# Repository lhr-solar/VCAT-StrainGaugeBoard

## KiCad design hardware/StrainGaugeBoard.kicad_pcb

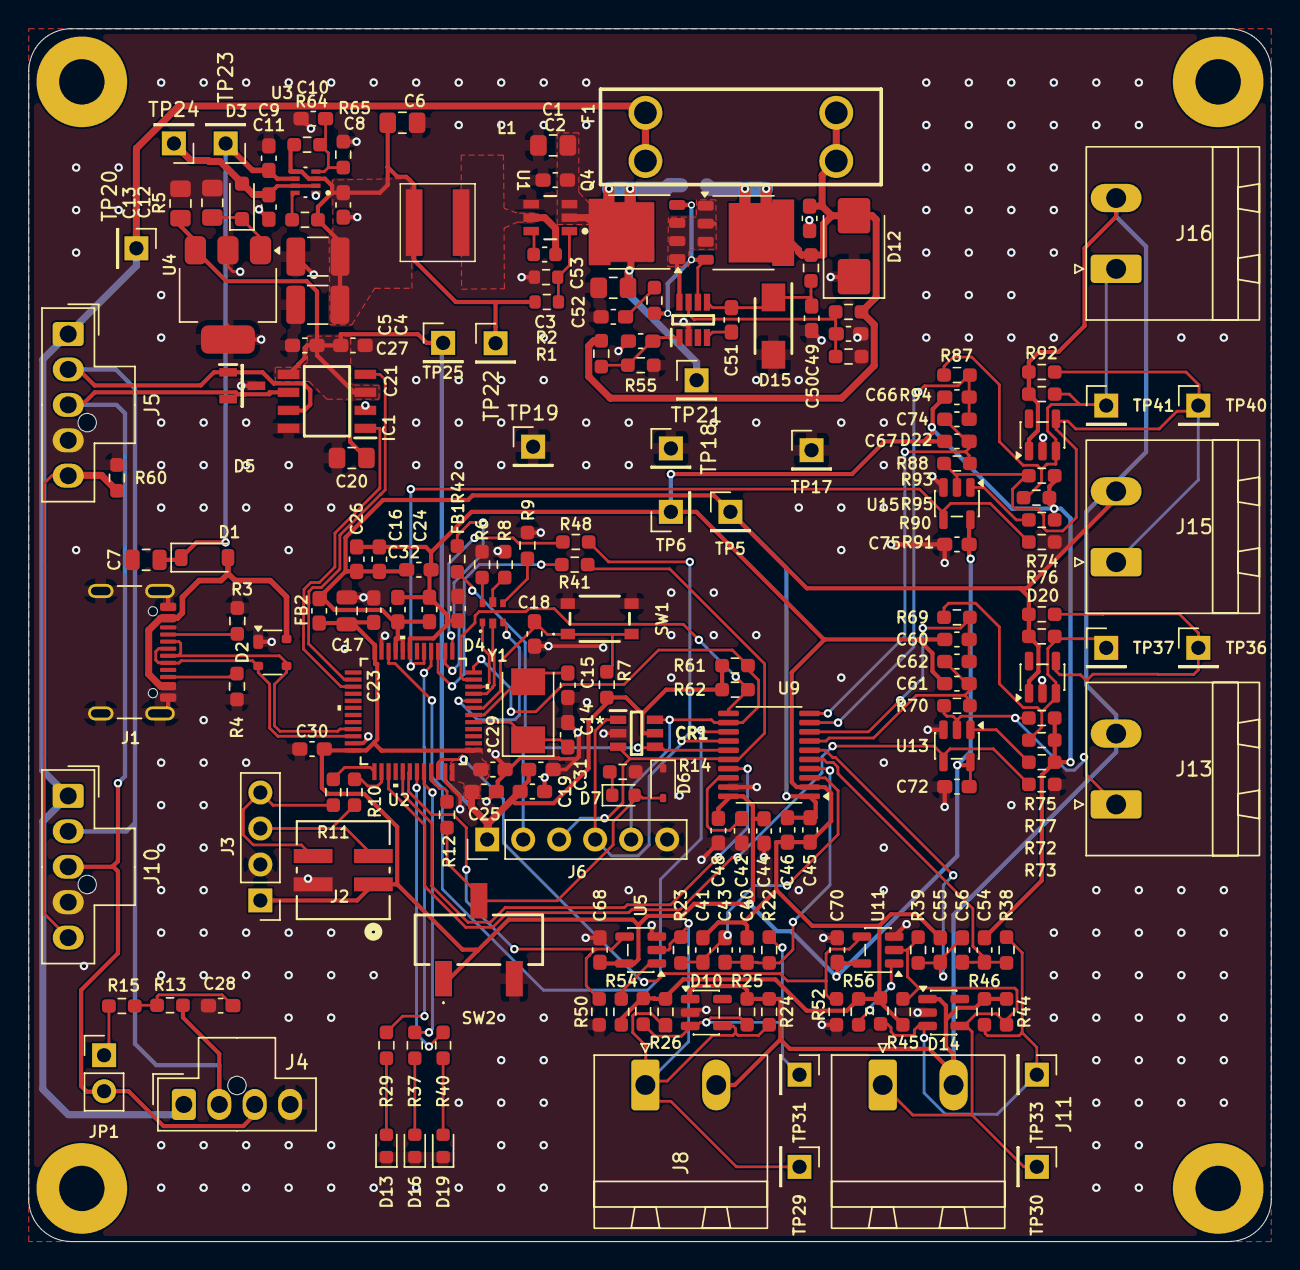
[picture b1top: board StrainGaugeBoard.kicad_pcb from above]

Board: 2 copper layers, 87.7 x 85.6 mm, 198 parts (1 on the bottom side), 92 nets.

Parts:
C1: 4.7u; C_0805_2012Metric_Pad1.18x1.45mm_HandSolder
C2: 100n; C_0603_1608Metric_Pad1.08x0.95mm_HandSolder
C3: 100n; C_0603_1608Metric
C4, C5: 22u; C_1210_3225Metric_Pad1.33x2.70mm_HandSolder
C6: 3.3u; C_0805_2012Metric_Pad1.18x1.45mm_HandSolder
C7: 10u; C_0805_2012Metric
C8, C9, C10, C11, C21, C27, C28, C45, C48, C49, C57, C58, C68, C70, C72, C75: 0.1u; C_0603_1608Metric_Pad1.08x0.95mm_HandSolder
C12, C13, C20, C53: 10u; C_0805_2012Metric_Pad1.18x1.45mm_HandSolder
C14, C15: 26p; C_0603_1608Metric_Pad1.08x0.95mm_HandSolder
C16, C18, C19, C22, C23, C25, C29, C30, C31: 0.1uF; C_0603_1608Metric_Pad1.08x0.95mm_HandSolder
C17: 10uF; C_0805_2012Metric
C24, C26: 1uF; C_0603_1608Metric_Pad1.08x0.95mm_HandSolder
C32: 100nF; C_0603_1608Metric_Pad1.08x0.95mm_HandSolder
C40, C41, C54, C55, C60, C61, C66, C67: 1n; C_0603_1608Metric_Pad1.08x0.95mm_HandSolder
C42, C51: 220n; C_0603_1608Metric_Pad1.08x0.95mm_HandSolder
C43, C52, C56, C62, C74: 10n; C_0603_1608Metric_Pad1.08x0.95mm_HandSolder
C44, C46, C50: 1u; C_0603_1608Metric_Pad1.08x0.95mm_HandSolder
CR1: D5V0P4UR6SO-7
D1: D_Schottky; D_SOD-123
D2: SP0503BAHT; SOT-143
D3: SBA130CH-AU_R1_000A1; D_SOD-323_HandSoldering
D4: RGB_LED
D5: CDSOT23-T24CAN
D6: TVS; D_SOD-323
D7, D13, D16, D19: LED; LED_0603_1608Metric
D10, D14, D20, D22: ESDA5V3SC5; SOT-23-5
D12: SMBJ15CA; D_SMB
D15: SMAF4758A; SODFL5026X125N
F1: 1A; Fuse-3557-2
FB1, FB2: FerriteBead; C_0603_1608Metric_Pad1.08x0.95mm_HandSolder
H1, H2, H3, H4: MountingHole_3.2mm_M3_Pad
IC1: TCAN3413DR
IC3: LM74502DDFR
J1: USB_C_Receptacle_USB2.0_16P; USB_C_Receptacle_GCT_USB4105-xx-A_16P_TopMnt_Horizontal
J2: SWD_Header; SWD_Conn
J3: SWD; PinHeader_1x04_P2.54mm_Vertical
J4: CAN_DEBUG; Molex_Nano-Fit_105309-xx04_1x04_P2.50mm_Vertical
J5: CAN_IN; Molex_Nano-Fit_105309-xx05_1x05_P2.50mm_Vertical
J6: Conn_01x06; PinHeader_1x06_P2.54mm_Vertical
J8, J11, J13: Gauge; PhoenixContact_MSTBA_2,5_2-G_1x02_P5.00mm_Horizontal
J10: CAN_OUT; Molex_Nano-Fit_105309-xx05_1x05_P2.50mm_Vertical
J15: Gauge A; PhoenixContact_MSTBA_2,5_2-G_1x02_P5.00mm_Horizontal
J16: Gauge B; PhoenixContact_MSTBA_2,5_2-G_1x02_P5.00mm_Horizontal
JP1: TRM; PinHeader_1x02_P2.54mm_Vertical
JP2: SolderJumper_2_Open; SolderJumper-2_P1.3mm_Open_RoundedPad1.0x1.5mm
L1: 8.2u; XAL5050822MEC
Q3, Q4: PSMN012-100YS; LFPAK56
R1: 100k; R_0603_1608Metric
R2: 19.1k; R_0603_1608Metric
R3, R4: 5.1k; R_0603_1608Metric_Pad0.98x0.95mm_HandSolder
R5, R7, R12, R35, R61, R62: 10k; R_0603_1608Metric_Pad0.98x0.95mm_HandSolder
R6, R8, R9, R14, R22, R23, R29, R37, R38, R39, R40, R69, R70, R87, R88: 1k; R_0603_1608Metric_Pad0.98x0.95mm_HandSolder
R10, R11, R41, R42, R48: 22; R_0603_1608Metric_Pad0.98x0.95mm_HandSolder
R13, R15: 60; R_0603_1608Metric_Pad0.98x0.95mm_HandSolder
R24, R25, R26, R27, R44, R45, R46, R47, R74, R75, R76, R77, R92, R93, R94, R95: 350; R_0603_1608Metric_Pad0.98x0.95mm_HandSolder
R36: 33; R_0603_1608Metric_Pad0.98x0.95mm_HandSolder
R49, R50, R52, R53, R73, R91: 100k; R_0603_1608Metric_Pad0.98x0.95mm_HandSolder
R51: 7.32k; R_0603_1608Metric_Pad0.98x0.95mm_HandSolder
R54, R56, R72, R90: 174k; R_0603_1608Metric_Pad0.98x0.95mm_HandSolder
R55: 15.8k; R_0603_1608Metric_Pad0.98x0.95mm_HandSolder
R60: 0; R_0603_1608Metric_Pad0.98x0.95mm_HandSolder
R64: 16k; R_0603_1608Metric_Pad0.98x0.95mm_HandSolder
R65: 4.7k; R_0603_1608Metric_Pad0.98x0.95mm_HandSolder
SW1: Reset; TL3365AF180QG
SW2: SW_SPDT; BootSW
TP5: VDDA; PinHeader_1x01_P2.54mm_Vertical
TP6: GNDA; PinHeader_1x01_P2.54mm_Vertical
TP17: Power TestPoint; PinHeader_1x01_P2.54mm_Vertical
TP18: MCU TestPoint; PinHeader_1x01_P2.54mm_Vertical
TP19: CAN TestPoint; PinHeader_1x01_P2.54mm_Vertical
TP20: +12V; PinHeader_1x01_P2.54mm_Vertical
TP21: +12V_PP; PinHeader_1x01_P2.54mm_Vertical
TP22: +5V_BUCK; PinHeader_1x01_P2.54mm_Vertical
TP23: +USBC_5V; PinHeader_1x01_P2.54mm_Vertical
TP24: MUX_OUT; PinHeader_1x01_P2.54mm_Vertical
TP25: LDO_OUT_TestPoint; PinHeader_1x01_P2.54mm_Vertical
TP29, TP30, TP36, TP40: SIG+; PinHeader_1x01_P2.54mm_Vertical
TP31, TP33, TP37, TP41: SIG-; PinHeader_1x01_P2.54mm_Vertical
U1: LMR51635XDDCR; DDC0006A-MFG
U2: STM32G473CETx; 48PinMCU
U3: TPS2117DRLR
U4: MCP1826S; SOT-223-3_TabPin2
U5, U11, U13, U15: TS5A3166DBVR; SOT-23-5
U9: ADS131M04xPW; TSSOP-20_4.4x6.5mm_P0.65mm
Y1: Crystal; Crystal_SMD_Abracon_ABM3-2Pin_5.0x3.2mm

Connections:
+3.3V: C13.2, C17.1, C19.1, C20.1, C21.1, C23.1, C25.1, C27.1, C29.1, C30.1, C31.1, C44.1, C48.1, C68.2, C70.2, C72.2, C75.2, CR1.5, FB2.1, IC1.3 (VCC), IC1.5 (SHDNV_IO), J2.1, J3.1, J6.1, R7.2, R61.1, R62.1, SW2.1 (A), TP25.1 (1_1), U2.1 (VBAT), U2.24 (VDD), U2.36 (VDD), U2.48 (VDD), U4.3 (VO), U5.5 (V+), U9.20 (DVDD), U11.5 (V+), U13.5 (V+), U15.5 (V+)
+5V: C11.1, D3.2 (A), TP24.1 (1_1), U3.2 (VOUT), U3.7 (VOUT__1)
+12V: F1.1, J4.1 (12V), J5.1 (12V), J10.1 (12V), TP20.1 (1_1)
/12VBuck/CB: C3.1, U1.6 (CB)
/12VBuck/FB: R1.2, R2.1, U1.1 (FB)
/12VBuck/SW: C3.2, L1.1, U1.5 (SW)
/48PinMCU/BOOT0: R12.1, U2.45 (PB8-BOOT0)
/48PinMCU/NRST: C18.1, R7.1, SW1.1, U2.7 (PG10-NRST)
/48PinMCU/PA0: D4.5, U2.8 (PA0-GPIO_BLUE)
/48PinMCU/PA1: D4.3, U2.9 (PA1_GPIO_RED)
/48PinMCU/PA2: D4.1, U2.10 (PA2-GPIO_GREEN)
/48PinMCU/PA5: R48.1, U2.13 (PA5)
/48PinMCU/PA6: R42.1, U2.14 (PA6)
/48PinMCU/PA7: R41.1, U2.15 (PA7)
/48PinMCU/PB0: R29.1, U2.16 (PB0)
/48PinMCU/PB6: R40.1, U2.43 (PB6)
/48PinMCU/PB7: R37.1, U2.44 (PB7)
/48PinMCU/SWCLK: R10.1, U2.38 (PA14)
/48PinMCU/SWDIO: R11.1, U2.37 (PA13)
/48PinMCU/USB_DM: D2.3 (K), J1.A7 (D-), J1.B7 (D-), U2.33 (PA11)
/48PinMCU/USB_DP: D2.2 (K), J1.A6 (D+), J1.B6 (D+), U2.34 (PA12)
/+5V_BUCK: C4.1, C5.1, C6.1, C8.1, L1.2, R1.1, R5.1, R64.1, TP22.1 (1_1), U3.3 (VIN1), U3.5 (MODE)
/+12V_PP: C1.1, C2.1, C53.1, JP2.2 (B), Q4.5, TP21.1 (1_1), U1.2 (EN), U1.3 (VIN)
/+USBC_5V: C7.2, C9.1, D1.1 (K), TP23.1 (1_1), U3.6 (VIN2)
/ADC_CLKIN: U2.41 (PB4), U9.17 (CLKIN)
/ADC_CS: CR1.6, J6.5, R61.2, U2.12 (PA4), U9.12 (~CS)
/ADC_DRDY: U2.22 (PB10), U9.13 (~DRDY)
/ADC_SYNC_RST: R62.2, U2.11 (PA3), U9.11 (~SYNC/~RESET)
/CAN_H: D5.1 (CAN_H), IC1.7 (CANH), J4.2 (CAN_H), J5.2 (CAN_H), J10.2 (CAN_H), R13.1
/CAN_L: D5.2 (CAN_L), IC1.6 (CANL), J4.3 (CAN_L), J5.3 (CAN_L), J10.3 (CAN_L), JP1.2 (B)
/CAN_RX: IC1.4 (RXD), U2.26 (PB12)
/CAN_TX: IC1.1 (TXD), U2.27 (PB13)
/PowerProtection/EN/UVLO: C58.1, IC3.1 (EN/UVLO), R53.2, R55.2
/PowerProtection/OV: C57.1, IC3.7 (OV), R49.2, R51.1
/PowerProtection/Vin: C49.1, D12.2 (A2), F1.2, JP2.1 (A), Q3.5, R35.2, R49.1, R53.1
/PowerProtection/gate: IC3.6 (GATE), Q3.4, Q4.4, R36.2
/PowerProtection/source: IC3.8 (SRC), Q3.1, Q3.2, Q3.3, Q4.1, Q4.2, Q4.3
/Power_Mux/PR1: C10.1, R64.2, R65.1, U3.4 (PR1)
/SHUNT_CAL0: R50.1, U2.42 (PB5), U5.4
/SHUNT_CAL1: R52.1, U2.46 (PB9), U11.4
/SHUNT_CAL2: R73.1, U2.39 (PA15), U13.4
/SHUNT_CAL3: R91.1, U2.17 (PB1), U15.4
/SPI_MISO: CR1.4, J6.2, R42.2, U9.15 (DOUT)
/SPI_MOSI: CR1.3, J6.3, R41.2, U9.16 (DIN)
/SPI_SCK: CR1.1, J6.4, R48.2, U9.14 (SCLK)
/StrainADC/AIN0N: C40.2, C43.2, R22.2, U9.4 (AIN0N)
/StrainADC/AIN0P: C41.2, C43.1, R23.2, U9.3 (AIN0P)
/StrainADC/AIN1N: C54.2, C56.2, R38.2, U9.5 (AIN1N)
/StrainADC/AIN1P: C55.2, C56.1, R39.2, U9.6 (AIN1P)
/StrainADC/AIN2N: C60.2, C62.2, R69.2, U9.8 (AIN2N)
/StrainADC/AIN2P: C61.2, C62.1, R70.2, U9.7 (AIN2P)
/StrainADC/AIN3N: C66.2, C74.2, R87.2, U9.9 (AIN3N)
/StrainADC/AIN3P: C67.2, C74.1, R88.2, U9.10 (AIN3P)
/StrainADC/StrainChannel0/SIG+: D10.4 (K), J8.1, R23.1, R24.2, R26.1, TP29.1 (1_1), U5.2
/StrainADC/StrainChannel0/SIG-: D10.3 (K), R22.1, R25.2, R27.1, TP31.1 (1_1)
/StrainADC/StrainChannel1/SIG+: D14.4 (K), J11.1, R39.1, R44.2, R45.1, TP30.1 (1_1), U11.2
/StrainADC/StrainChannel1/SIG-: D14.3 (K), R38.1, R46.2, R47.1, TP33.1 (1_1)
/StrainADC/StrainChannel2/SIG+: D20.4 (K), J13.1, R70.1, R74.2, R75.1, TP36.1 (1_1), U13.2
/StrainADC/StrainChannel2/SIG-: D20.3 (K), R69.1, R76.2, R77.1, TP37.1 (1_1)
/StrainADC/StrainChannel3/SIG+: D22.4 (K), J15.1, R88.1, R92.2, R93.1, TP40.1 (1_1), U15.2
/StrainADC/StrainChannel3/SIG-: D22.3 (K), J16.1, R87.1, R94.2, R95.1, TP41.1 (1_1)
/USB-C_Connector/CC1: J1.A5 (CC1), R3.2
/USB-C_Connector/CC2: J1.B5 (CC2), R4.2
/USB-C_Connector/VBUS_IN: D1.2 (A), D2.4 (K), J1.A4 (VBUS), J1.A9 (VBUS), J1.B4 (VBUS), J1.B9 (VBUS)
/VDDA: C16.1, C22.1, C24.1, C26.1, C32.1, C45.1, C46.1, D10.1 (K), D14.1 (K), D20.1 (K), D22.1 (K), FB2.2, J8.2, J11.2, J13.2, J15.2, J16.2, R24.1, R25.1, R44.1, R46.1, R74.1, R76.1, R92.1, R94.1, TP5.1 (1_1), U2.20 (VREF+), U2.21 (VDDA), U9.1 (AVDD)
GND: C1.2, C2.2, C4.2, C5.2, C6.2, C7.1, C8.2, C9.2, C10.2, C11.2, C12.1, C13.1, C14.1, C15.2, C17.2, C18.2, C19.2, C20.2, C21.2, C23.2, C25.2, C27.2, C28.1, C29.2, C30.2, C31.2, C42.2, C44.2, C48.2, C49.2, C50.1, C52.2, C53.2, C57.2, C58.2, C68.1, C70.1, C72.1, C75.1, CR1.2, D2.1 (A), D5.3 (GND), D6.1 (A1), D10.2 (A), D12.1 (A1), D13.1 (K), D14.2 (A), D15.2 (A), D16.1 (K), D19.1 (K), D20.2 (A), D22.2 (A), FB1.2, IC1.2 (GND), IC1.8 (STB), IC3.2 (GND), J1.A1 (GND), J1.A12 (GND), J1.B1 (GND), J1.B12 (GND), J1.S1 (SHIELD), J1.S2 (Shield), J1.S3 (Shield), J1.S4 (Shield), J2.2, J3.2, J4.4 (GND), J5.4 (GND), J6.6, J10.4 (GND), R2.2, R3.1, R4.1, R6.2, R8.2, R9.2, R14.2, R50.2, R51.2, R52.2, R55.1, R60.2, R65.2, R73.2, R91.2, SW1.2, SW2.3 (C), TP17.1 (1_1), TP18.1 (1_1), TP19.1 (1_1), U1.4 (GND), U2.23 (VSS), U2.35 (VSS), U2.47 (VSS), U3.1 (GND), U4.2 (GND), U5.3 (GND), U9.19 (DGND), U11.3 (GND), U13.3 (GND), U15.3 (GND)
GNDA: C16.2, C22.2, C24.2, C26.2, C32.2, C40.1, C41.1, C45.2, C46.2, C54.1, C55.1, C60.1, C61.1, C66.1, C67.1, FB1.1, R26.2, R27.2, R45.2, R47.2, R54.2, R56.2, R72.2, R75.2, R77.2, R90.2, R93.2, R95.2, TP6.1 (1_1), U2.19 (VSSA), U9.2 (AGND)
unnamed: C28.2, R13.2, R15.1
unnamed: C52.1, R36.1
unnamed: C12.2, D3.1 (K), U4.1 (VI)
unnamed: D4.2, R6.1
unnamed: D4.4, R8.1
unnamed: D4.6, R9.1
unnamed: D6.2 (A2), D7.2 (A), R12.2, SW2.2 (B)
unnamed: D7.1 (K), R14.1
unnamed: D13.2 (A), R29.2
unnamed: C50.2, C51.1, D15.1 (K), IC3.5 (VS), R35.1
unnamed: D16.2 (A), R37.2
unnamed: D19.2 (A), R40.2
unnamed: C51.2, IC3.4 (VCAP)
unnamed: J2.3, J3.3, R10.2
unnamed: J2.4, J3.4, R11.2
unnamed: J5.5 (SHIELD), J10.5 (SHIELD), R60.1
unnamed: JP1.1 (A), R15.2
unnamed: R54.1, U5.1
unnamed: R56.1, U11.1
unnamed: R72.1, U13.1
unnamed: R90.1, U15.1
unnamed: C14.2, U2.5 (PF0-OSC_IN), Y1.1
unnamed: C15.1, U2.6 (PF1-OSC_OUT), Y1.2
unnamed: R5.2, U3.8 (ST)
unnamed: C42.1, U9.18 (CAP)

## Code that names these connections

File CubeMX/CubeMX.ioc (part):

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Mcu.Name=STM32G473C(B-C-E)Tx
Mcu.Package=LQFP48
Mcu.UserName=STM32G473CETx
PA0.GPIOParameters=GPIO_Label
PA0.GPIO_Label=LED_B
PA0.Signal=S_TIM2_CH1
PA1.GPIOParameters=GPIO_Label
PA1.GPIO_Label=LED_R
PA1.Signal=S_TIM2_CH2
PA10.GPIOParameters=GPIO_Label
PA10.GPIO_Label=SHUNT_CAL1
PA10.Signal=GPIO_Output
PA11.Mode=Device
PA11.Signal=USB_DM
PA12.Mode=Device
PA12.Signal=USB_DP
PA13.Mode=Serial_Wire
PA13.Signal=SYS_JTMS-SWDIO
PA14.Mode=Serial_Wire
PA14.Signal=SYS_JTCK-SWCLK
PA15.GPIOParameters=GPIO_Label
PA15.GPIO_Label=SHUNT_CAL2
PA15.Signal=GPIO_Output
PA2.GPIOParameters=GPIO_Label
PA2.GPIO_Label=LED_G
PA2.Signal=S_TIM2_CH3
PA4.GPIOParameters=PinState,GPIO_Label
PA4.GPIO_Label=ADC_CS
PA4.PinState=GPIO_PIN_SET
PA4.Signal=GPIO_Output
PA5.Mode=Full_Duplex_Master
PA5.Signal=SPI1_SCK
PA6.Mode=Full_Duplex_Master
PA6.Signal=SPI1_MISO
PA7.Mode=Full_Duplex_Master
PA7.Signal=SPI1_MOSI
PA8.GPIOParameters=GPIO_Label
PA8.GPIO_Label=ADC_CLKIN
PA8.Mode=Clock-out
PA8.Signal=RCC_MCO
PA9.GPIOParameters=GPIO_Label
PA9.GPIO_Label=SHUNT_CAL0
PA9.Signal=GPIO_Output
PB0.GPIOParameters=GPIO_Label
PB0.GPIO_Label=LED_STATUS
PB0.Signal=GPIO_Output
PB1.GPIOParameters=GPIO_Label
PB1.GPIO_Label=SHUNT_CAL3
PB1.Signal=GPIO_Output
PB10.GPIOParameters=GPIO_Label,GPIO_ModeDefaultEXTI
PB10.GPIO_Label=ADC_DRDY
PB10.GPIO_ModeDefaultEXTI=GPIO_MODE_IT_FALLING
PB10.Signal=GPXTI10
PB11.GPIOParameters=PinState,GPIO_Label
PB11.GPIO_Label=ADC_SYNC_RST
PB11.PinState=GPIO_PIN_SET
PB11.Signal=GPIO_Output
PB12.GPIOParameters=GPIO_Label
PB12.GPIO_Label=CAN_RX
PB12.Mode=FDCAN_Activate
PB12.Signal=FDCAN2_RX
PB13.GPIOParameters=GPIO_Label
PB13.GPIO_Label=CAN_TX
PB13.Mode=FDCAN_Activate
PB13.Signal=FDCAN2_TX
PB6.GPIOParameters=GPIO_Label
PB6.GPIO_Label=LED2
PB6.Signal=GPIO_Output
PB7.GPIOParameters=GPIO_Label
PB7.GPIO_Label=LED1
PB7.Signal=GPIO_Output
PF0-OSC_IN.Mode=HSE-External-Oscillator
PF0-OSC_IN.Signal=RCC_OSC_IN
PF1-OSC_OUT.Mode=HSE-External-Oscillator
PF1-OSC_OUT.Signal=RCC_OSC_OUT
RCC.HSE_VALUE=8000000
RCC.SYSCLKFreq_VALUE=16000000
board=custom
